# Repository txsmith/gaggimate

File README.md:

This project upgrades a Gaggia espresso machine with smart controls to improve your coffee-making experience. By adding a display and custom electronics, you can monitor and control the machine more easily.

## Features

- **Temperature Control**: Monitor the boiler temperature to ensure optimal brewing conditions.
- **Brew timer**: Set a target duration and run the brewing for the specific time.
- **Steam and Hot Water mode**: Control the pump and valve to run the respective task.
- **Safety Features**: Automatic shutoff if the system becomes unresponsive or overheats.
- **User Interface**: Simple, intuitive display to control and monitor the machine.

## Screenshots

## Hardware

- **Gaggia Espresso Machine**
- **LilyGo T-RGB 2.1" Display**: Runs the user interface and communicates with the system.
- **ESP-WROOM32 DevKit**: Handles the machine’s low-level control.
- **K-Type M4 Thermocouple with MAX6675**: Reads the temperature of the boiler.
- **AC SSR**: Controls the heating element (boiler).
- **2-Channel 5V Relay**: Controls the pump and valve.

## How It Works

The display allows you to control the espresso machine and see live temperature updates. If the machine becomes unresponsive or the temperature goes too high, it will automatically turn off for safety.

## Installation

1. Connect the ESP32-S3 Display, ESP-WROOM32 DevKit, and other components to the Gaggia.
2. Upload the firmware to both microcontrollers.
3. Enjoy your smarter coffee-making experience!

## License

This work is licensed under CC BY-NC-SA 4.0. To view a copy of this license, visit https://creativecommons.org/licenses/by-nc-sa/4.0/

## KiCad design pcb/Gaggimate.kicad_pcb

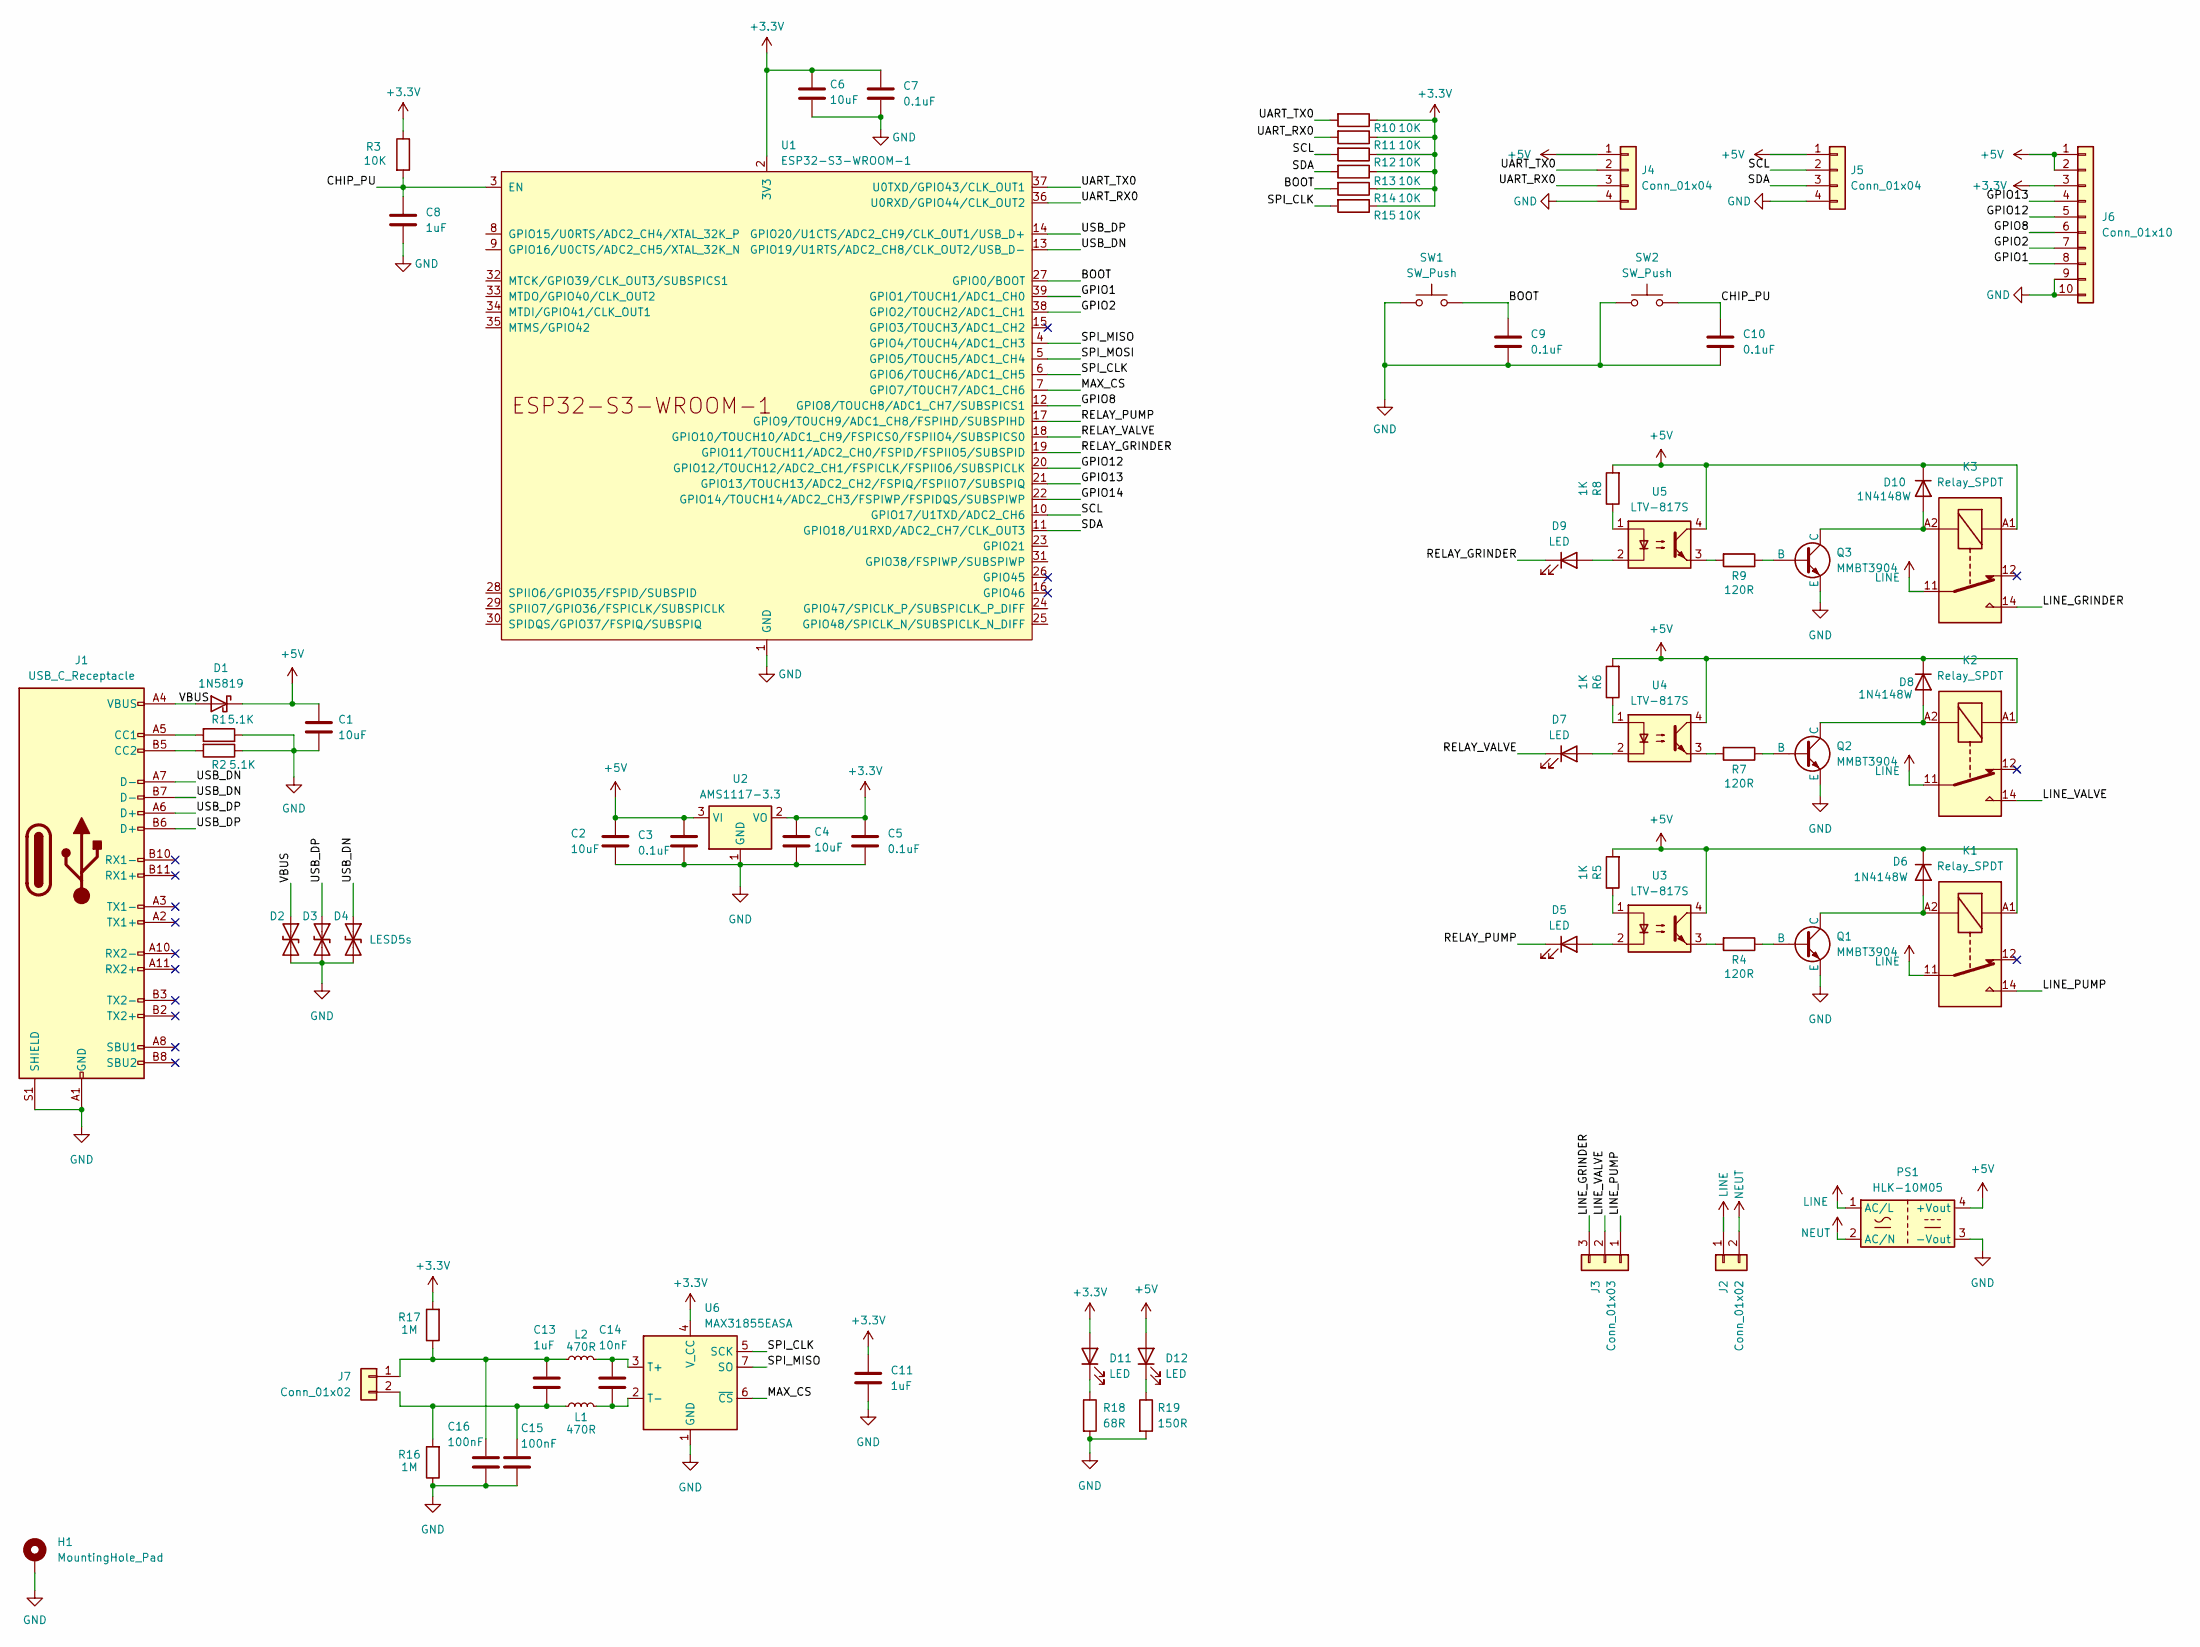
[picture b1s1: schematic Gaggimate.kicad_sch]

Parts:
C1, C2, C4, C6: 10uF; C_0805_2012Metric
C3, C5, C7, C9, C10: 0.1uF; C_0805_2012Metric
C8, C11, C13: 1uF; C_0805_2012Metric
C14: 10nF; C_0805_2012Metric
C15, C16: 100nF; C_0805_2012Metric
D1: 1N5819; D_SOD-123
D2, D3, D4: LESD5s; D_SOD-523
D5, D7, D9, D11, D12: LED; LED_0805_2012Metric
D6, D8, D10: 1N4148W; D_SOD-123
H1: MountingHole_Pad; MountingHole_3.2mm_M3_DIN965_Pad_TopBottom
J1: USB_C_Receptacle; USB_C_Receptacle_HRO_TYPE-C-31-M-12
J2: Conn_01x02; TerminalBlock_bornier-2_P5.08mm
J3: Conn_01x03; TerminalBlock_bornier-3_P5.08mm
J4, J5: Conn_01x04; JST_XH_B4B-XH-A_1x04_P2.50mm_Vertical
J6: Conn_01x10; PinHeader_1x10_P2.54mm_Vertical
J7: Conn_01x02; TerminalBlock_Phoenix_PT-1,5-2-3.5-H_1x02_P3.50mm_Horizontal
K1, K2, K3: Relay_SPDT; Relay_SPDT_Finder_36.11
L1, L2: 470R; L_0805_2012Metric
PS1: HLK-10M05; Converter_ACDC_HiLink_HLK-10Mxx
Q1, Q2, Q3: MMBT3904; SOT-23-3
R1, R2: 5.1K; R_0805_2012Metric
R3, R10, R11, R12, R13, R14, R15: 10K; R_0805_2012Metric
R4, R7, R9: 120R; R_0805_2012Metric
R5, R6, R8: 1K; R_0805_2012Metric
R16, R17: 1M; R_0805_2012Metric
R18: 68R; R_0805_2012Metric
R19: 150R; R_0805_2012Metric
SW1, SW2: SW_Push; SW_SPST_PTS810
U1: ESP32-S3-WROOM-1
U2: AMS1117-3.3; SOT-223-3_TabPin2
U3, U4, U5: LTV-817S; SMDIP-4_W9.53mm
U6: MAX31855EASA; SOIC-8_3.9x4.9mm_P1.27mm

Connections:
+3.3V: C4.1, C5.1, C6.1, C7.1, C11.1, D11.2 (A), J6.3, R3.1, R10.1, R11.1, R12.1, R13.1, R14.1, R15.1, R17.2, U1.2 (3V3), U2.2 (VO), U6.4 (V_CC)
+5V: C1.1, C2.1, C3.1, D1.1 (K), D6.1 (K), D8.1 (K), D10.1 (K), D12.2 (A), J4.1, J5.1, J6.1, J6.2, K1.A1, K2.A1, K3.A1, PS1.4 (+Vout), R5.2, R6.2, R8.2, U2.3 (VI), U3.4, U4.4, U5.4
/BOOT: C9.1, R14.2, SW1.2, U1.27 (GPIO0/BOOT)
/CHIP_PU: C8.1, C10.1, R3.2, SW2.2, U1.3 (EN)
/GPIO1: J6.8, U1.39 (GPIO1/TOUCH1/ADC1_CH0)
/GPIO2: J6.7, U1.38 (GPIO2/TOUCH2/ADC1_CH1)
/GPIO8: J6.6, U1.12 (GPIO8/TOUCH8/ADC1_CH7/SUBSPICS1)
/GPIO12: J6.5, U1.20 (GPIO12/TOUCH12/ADC2_CH1/FSPICLK/FSPIIO6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)
/GPIO13: J6.4, U1.21 (GPIO13/TOUCH13/ADC2_CH2/FSPIQ/FSPIIO7/S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)
/GPIO14: U1.22 (GPIO14/TOUCH14/ADC2_CH3/FSPIWP/FSPIDQS/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)
/LINE_GRINDER: J3.3, K3.14
/LINE_PUMP: J3.1, K1.14
/LINE_VALVE: J3.2, K2.14
/MAX_CS: U1.7 (GPIO7/TOUCH7/ADC1_CH6), U6.6 (~CS)
/RELAY_GRINDER: D9.1 (K), U1.19 (GPIO11/TOUCH11/ADC2_CH0/FSPID/FSPIIO5/S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)
/RELAY_PUMP: D5.1 (K), U1.17 (GPIO9/TOUCH9/ADC1_CH8/FSPIHD/SUBSPIHD)
/RELAY_VALVE: D7.1 (K), U1.18 (GPIO10/TOUCH10/ADC1_CH9/FSPICS0/FSPIIO4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)
/SCL: J5.2, R12.2, U1.10 (GPIO17/U1TXD/ADC2_CH6)
/SDA: J5.3, R13.2, U1.11 (GPIO18/U1RXD/ADC2_CH7/CLK_OUT3)
/SPI_CLK: R15.2, U1.6 (GPIO6/TOUCH6/ADC1_CH5), U6.5 (SCK)
/SPI_MISO: U1.4 (GPIO4/TOUCH4/ADC1_CH3), U6.7 (SO)
/SPI_MOSI: U1.5 (GPIO5/TOUCH5/ADC1_CH4)
/UART_RX0: J4.3, R11.2, U1.36 (U0RXD/GPIO44/CLK_OUT2)
/UART_TX0: J4.2, R10.2, U1.37 (U0TXD/GPIO43/CLK_OUT1)
/USB_DN: D4.1 (A1), J1.A7 (D-), J1.B7 (D-), U1.13 (GPIO19/U1RTS/ADC2_CH8/CLK_OUT2/USB_D-)
/USB_DP: D3.1 (A1), J1.A6 (D+), J1.B6 (D+), U1.14 (GPIO20/U1CTS/ADC2_CH9/CLK_OUT1/USB_D+)
/VBUS: D1.2 (A), D2.1 (A1), J1.A4 (VBUS), J1.A9 (VBUS), J1.B4 (VBUS), J1.B9 (VBUS)
GND: C1.2, C2.2, C3.2, C4.2, C5.2, C6.2, C7.2, C8.2, C9.2, C10.2, C11.2, C15.2, C16.2, D2.2 (A2), D3.2 (A2), D4.2 (A2), H1.1, J1.A1 (GND), J1.A12 (GND), J1.B1 (GND), J1.B12 (GND), J1.S1 (SHIELD), J4.4, J5.4, J6.9, J6.10, PS1.3 (-Vout), Q1.3 (E), Q2.3 (E), Q3.3 (E), R1.1, R2.1, R16.1, R18.2, R19.2, SW1.1, SW2.1, U1.1 (GND), U1.40 (GND), U1.41 (GND), U2.1 (GND), U6.1 (GND); also elsewhere on the board
LINE: J2.1, K1.11, K2.11, K3.11, PS1.1 (AC/L)
NEUT: J2.2, PS1.2 (AC/N)
unnamed: D5.2 (A), U3.2
unnamed: D6.2 (A), K1.A2, Q1.1 (C)
unnamed: D7.2 (A), U4.2
unnamed: D8.2 (A), K2.A2, Q2.1 (C)
unnamed: D9.2 (A), U5.2
unnamed: D10.2 (A), K3.A2, Q3.1 (C)
unnamed: D11.1 (K), R18.1
unnamed: D12.1 (K), R19.1
unnamed: J1.A5 (CC1), R1.2
unnamed: J1.B5 (CC2), R2.2
unnamed: C13.1, C16.1, J7.1, L2.1, R17.1
unnamed: C13.2, C15.1, J7.2, L1.1, R16.2
unnamed: Q1.2 (B), R4.1
unnamed: Q2.2 (B), R7.1
unnamed: Q3.2 (B), R9.1
unnamed: R4.2, U3.3
unnamed: R5.1, U3.1
unnamed: R6.1, U4.1
unnamed: R7.2, U4.3
unnamed: R8.1, U5.1
unnamed: R9.2, U5.3
unnamed: C14.1, L2.2, U6.3 (T+)
unnamed: C14.2, L1.2, U6.2 (T-)

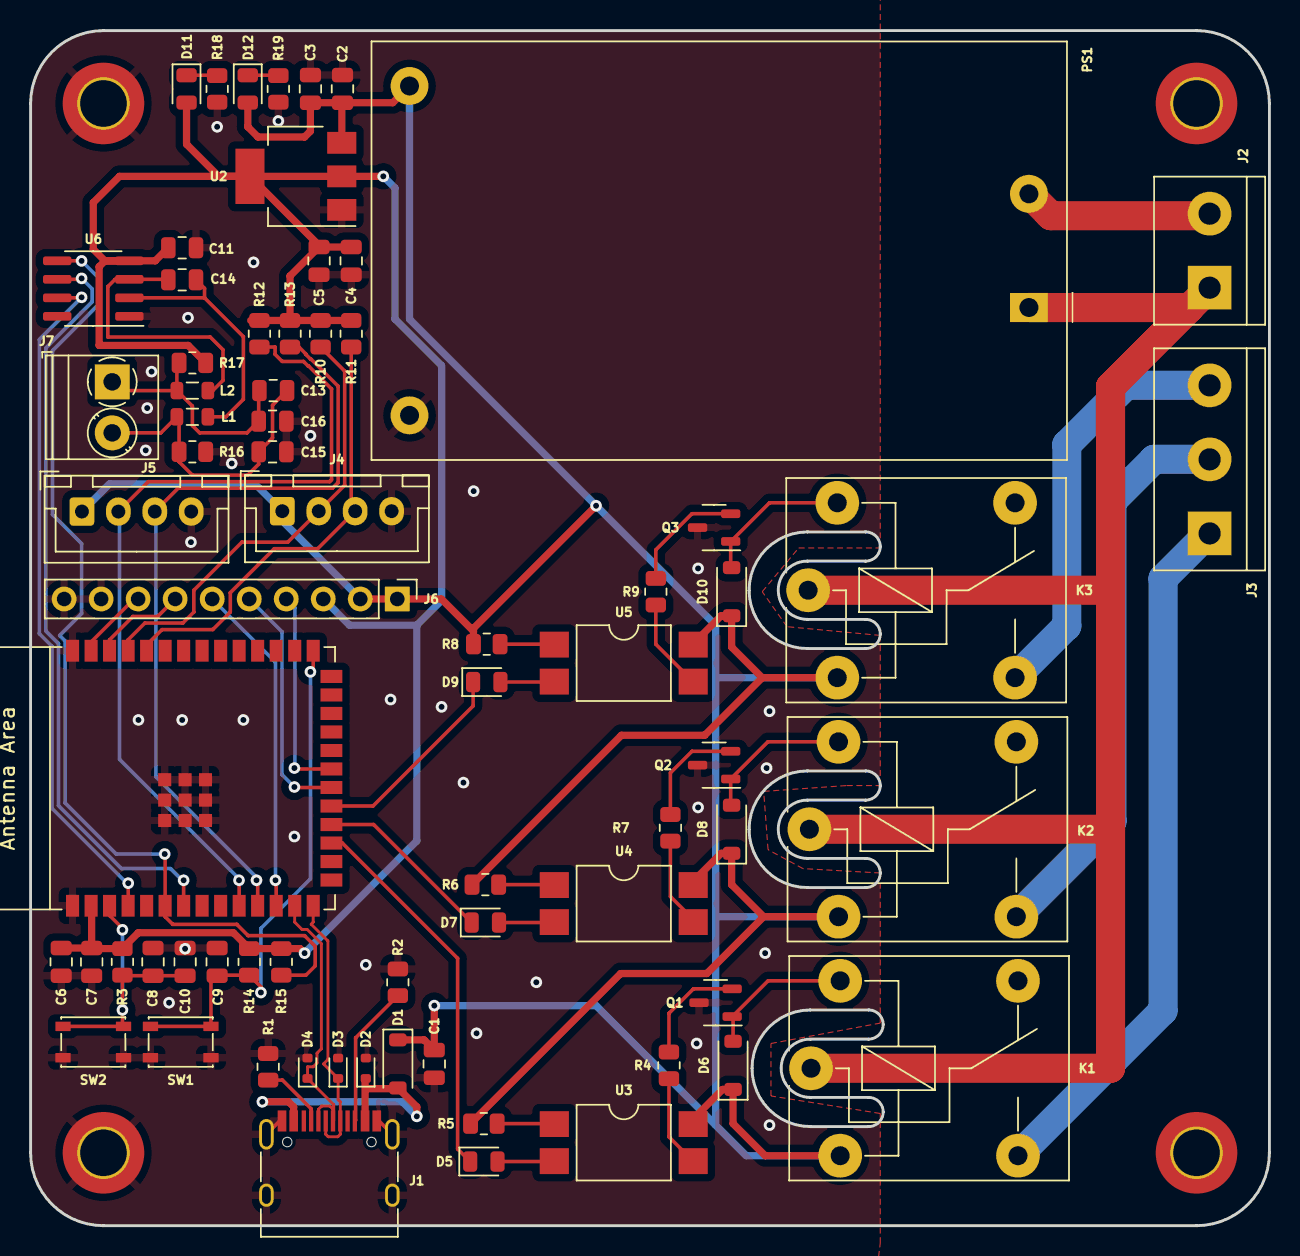
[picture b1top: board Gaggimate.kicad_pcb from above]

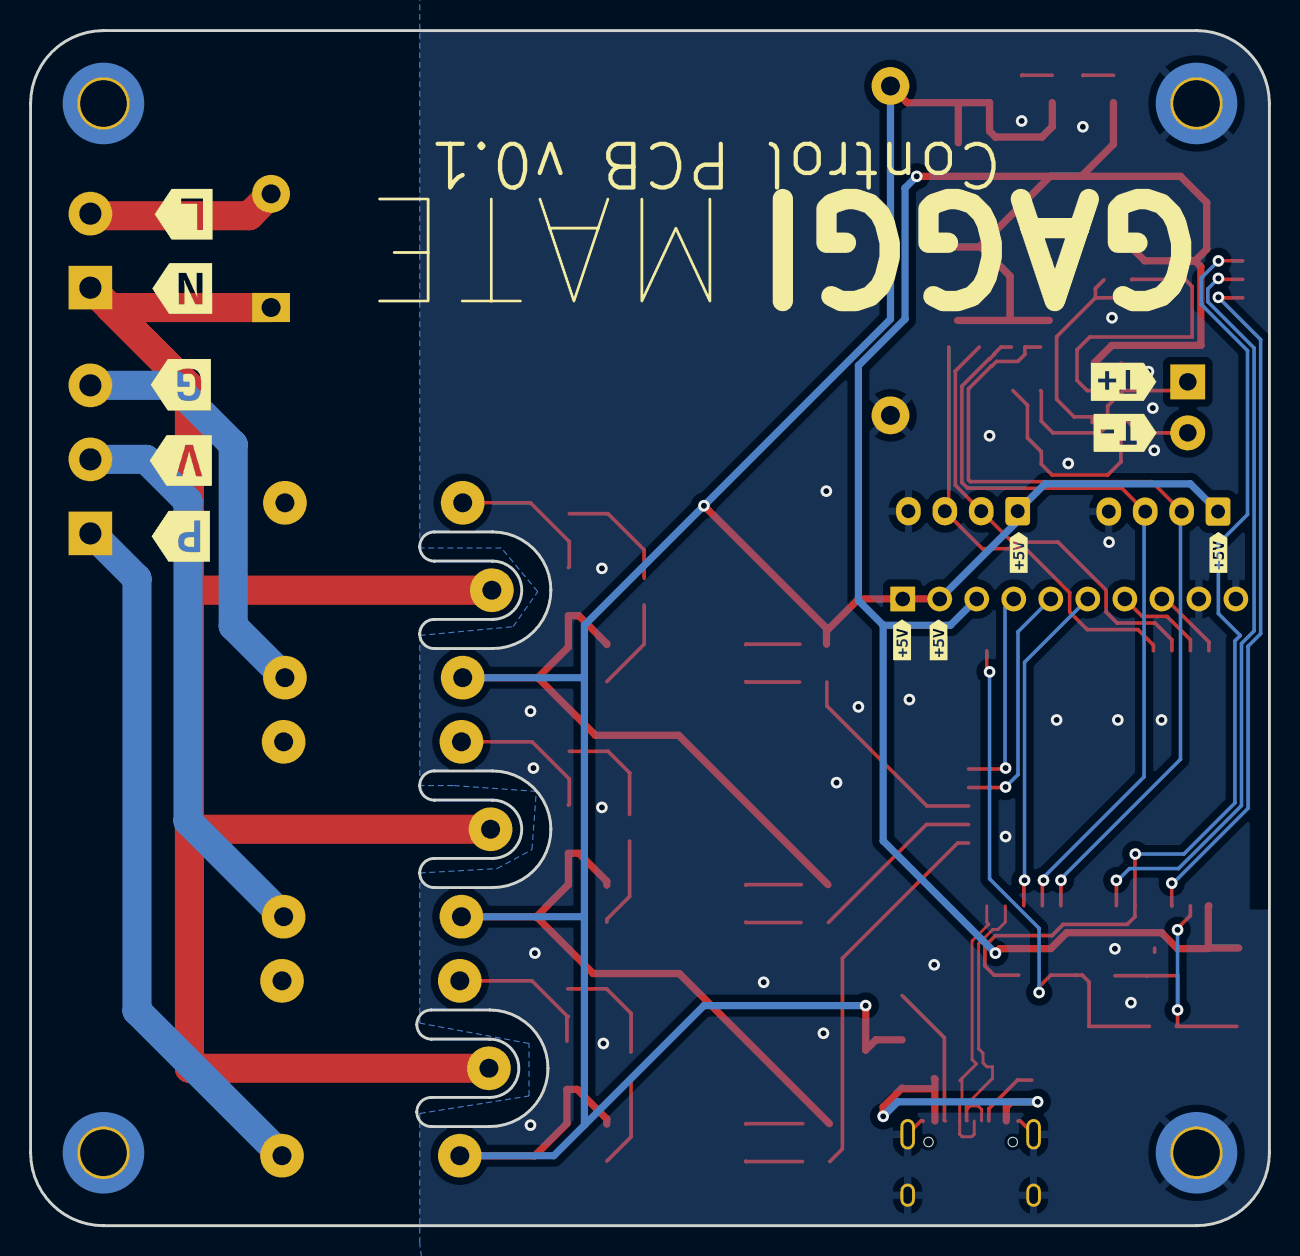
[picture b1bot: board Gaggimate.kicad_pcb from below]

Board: 2 copper layers, 85.0 x 82.0 mm, 85 parts (11 on the bottom side), 51 nets.

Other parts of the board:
H1#2, H1#3, H1#4: MountingHole_Pad; MountingHole_3.2mm_M3_DIN965_Pad_TopBottom
kibuzzard-671E8BF3: G***; kibuzzard-671E8BF3
kibuzzard-671E8C00: G***; kibuzzard-671E8C00
kibuzzard-671E8C4D: G***; kibuzzard-671E8C4D
kibuzzard-671E8C14: G***; kibuzzard-671E8C14
kibuzzard-671E8C44: G***; kibuzzard-671E8C44
kibuzzard-671E8D02, kibuzzard-671E8D02#2, kibuzzard-671E8D02#3, kibuzzard-671E8D02#4: G***; kibuzzard-671E8D02
kibuzzard-671EE717: G***; kibuzzard-671EE717
kibuzzard-671EE722: G***; kibuzzard-671EE722

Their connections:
GND: H1#4.1; also elsewhere on the board

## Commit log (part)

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2024-11-24 fix: Move back connectors to allow expansion to fit
2024-11-24 fix: Fix AC line
2024-11-26 chore: Fix sonarqube issues #2
2024-11-26 chore: Fix sonarqube issues #5
2024-11-27 feat: Rework OTA library, use SPIFFS for web
2024-11-27 doc: Add sonarqube badges
2024-11-27 fix: Fix style css
2024-11-28 fix: Remove auto update for now
2024-12-02 fix: Simplify OTA
2024-12-02 feat: Add wiring diagrams
2024-12-10 feat: Remove docs from readme
2024-12-11 fix: Fix rotation calculation
2024-12-17 fix: Fix partition table for controller
2024-12-19 feat: Finalize first Github OTA functionality
2024-12-19 feat: Add OTA improvements, BLE OTA receiver code
2024-12-19 fix: Fix display build with BLE ota
2024-12-26 Added variant without screwholes
    This screen backplate model fits the GCP better, by having magnets placed lower. This is a version without screw holes.
2025-01-11 feat: Refactor UI code
2025-01-11 fix: Ignore data files
2025-01-12 feat: Add UI changes for volumetric target
2025-01-12 feat: Add BLE scale library
2025-01-14 feat: Rework UI, add waveshare driver, add BLE preparation
2025-01-17 fix: Remove reset
2025-01-18 feat: Allow skipping preinfusion
2025-01-18 fix: Fix formatting
2025-01-20 fix: Clean up brew phase code
2025-01-25 fix: Fix pid bug with temp offset
2025-01-30 feat: Pre-infusion now pumps with the valve open
2025-01-30 feat: Add plugin for automatic boiler refill
2025-01-30 fix: Fix ui files
2025-01-31 feat: Add simple predictive scale feature
2025-02-01 fix: Raise predictive time
2025-02-01 feat: Add MQTT integration with new Web UI
2025-02-01 Aading mqtt user and password
    WIP
2025-02-01 MQTT fix
2025-02-01 fix: Fix sonarqube issue
2025-02-01 fix: Fix header declaration
2025-02-04 fix: Use flex grow for progress bars instead of pixels
2025-02-05 feat: Allow to configure pressurize time
2025-02-05 fix: Fix predictive flow
2025-02-05 fix: Fix filesystem OTA
2025-02-11 fix: Cleanup before board v2
2025-02-15 Added grind mode
2025-03-09 feat: Add felicita arc, fix Eureka scales
2025-03-15 feat: Add button control (#139)
    * added brew button on
    * brew button functionality
    * added steam button actions
    * revert dev changes
    * revert
    * feat: Finish button control code
2025-03-16 feat: Add temperature graph to web ui (#143)
2025-03-16 fix: Fix adding nightly version
    * fix: Add nightly version to build
    * fix: Fix adding version to nightly
2025-03-16 fix: Fix build
2025-03-16 feat: Raise weight output limit to 250 (#149)
    Fixes #138
2025-03-17 fix: Fix captive portal (#152)
    * fix: Fix captive portal
    * fix: Remove unused HTML
2025-03-18 fix: Raise delay between OTA messages
2025-03-19 fix: Add LPF for heater
2025-03-19 feat: Fix v1.4.0 bugs, add better scale and grind control (#158)
2025-04-01 Fixed indent
    Fixed indent
2025-04-01 fix: Fix jumping into brewscreen (#168)
    Fixes #160
2025-04-06 fix: Fix freertos includes
2025-04-06 feat: Make standby timeout configurable (#172)
    Fixes #120
2025-04-10 feat: Add PID Autotune (#176)
    * feat: Add profile edit screen
    * feat: Add PID Autotune
    * fix: Hide future menu options again
    * fix: Remove unused css
2025-05-01 fix: Fix dark mode display of web ui (#182)
2025-05-19 fix: Fix PID heater
2025-05-24 feat: Add pressure gauge, optimize communication (#205)
    * feat: Add pressure display
    * feat: Merge sensor and control data
    * feat: Adjust UI depending on board version
2025-05-29 feat: Improve/fix pump on standard v2, cleanup BLE comms (#210)
2025-06-03 fix: Remove extra options from pid
2025-06-03 fix: Fix nightly workflow
2025-06-06 Add dark background option for profile div (#231)
2025-06-06 fix: Prevent empty favorites
2025-06-06 fix: Fix null division bugs
2025-06-13 fix: Swap out PSM library
2025-06-13 feat: Add styled tooltips
2025-06-14 fix: Add minimum of 1 to duration
2025-06-14 Pressure scaling UI fixes (#235)
    * feat: Introduce profiles (#175)
    * feat: Add profile edit screen
    * fix: Fix merge errors
    * feat: Add new profile screen
    * fix: Fix PID heater
    * feat: Add profile progress
2025-06-15 feat: Set grinder adjustment to 0.5g instead of 1g (#245)
2025-06-16 feat: Add Nayrods pump control, flow estimation and volume estimation (#251)
    * feat: Add Nayrods pump control, flow estimation and volume estimation
    * fix: Fix test warning
    * fix: Fix volume estimation
    * feat: Add pressure and flow graphs to web ui
    * fix: Fix controller usage
2025-06-16 fix: Fix duplicate CSS
2025-06-27 Allowing any float value for the auto adjust brew and grind delay values. (#265)
2025-06-29 feat: Steam Rework and temperature indicator (#277)
    * feat: Redesign UI for new steam mode
    * Make it green (when ready) (#272)
    * feat: Add UI Changes
    * feat: Make steam pump percentage adjustable
    * feat: Change button control for steam mode
    * feat: Major UI speedup, add auto steam
2025-06-30 fix: Update asynctcp, fix websocket reconnect
2025-06-30 fix: Make pressure bar smoother
2025-06-30 fix: Autoconnect scale when startup mode is brew (#280)
2025-07-04 Add NayrodPID as a submodule
2025-07-09 Hydraulic estimation Kalman based, turbulent flow model
2025-07-09 fix: Remove unused wifi manager
2025-07-09 feat: Allow experimental features to stay in releases (#294)
2025-07-09 fix: Fix wrong flow when no brew is running
2025-07-10 fix: Initialize wifi last
2025-07-10 fix: Fix too verbose logging
2025-07-11 fix: Replace wifi manager
2025-07-13 Fix Chart resize on screen rotation (#303)
2025-07-14 Update BLEScalePlugin.cpp for WeighMyBru Scale Support (#284)
    * Update BLEScalePlugin.cpp for WeighMyBru Scale Support
    * Added WeighMyBru Scale Support & Updated platformio.ini
    * Changed platformio.ini file back to original
    ---------
2025-07-14 Add display theme application via WebUI (#282)
    * Add theme application
    * Revert SLS edit
    * Fix newlines
    * Fix settings, change colors
    * No need to trigger dirty
2025-07-14 feat: Add first shot on history (#297)
    * feat: Add first shot on history
    * fix: Fix too verbose logging
    * fix: Fix too verbose error logging
    * feat: Finish first shot of shot history
    * fix: Fix data change
    * fix: Fix estimator
2025-07-17 Move Save Preferences button on OTA page and fix overflow issues (#305)
    * move "Save preferences" button on OTA page, fix overflow issues on OTA and Settings page
    The only real changes are to /web/src/pages/OTA/index.jsx and /web/src/pages/Settings/index.jsx, the rest are from running the prettier command
    Moved the "Save preferences" button to the div containing the Update channel selector to clarify that the button saves the update channel chosen
    Added flex-wrap and gap-y-2 to the div containing the Update-buttons to allow the buttons to stack vertically when there is not enough width to stack them horizontally
    * change flex gap to gap-y-1 on container for Update-buttons to match gap be
2025-07-22 feat: Turn down Autotune shutoff temp (#313)
    * feat: Turn down Autotune shutoff temp
    * fix: Implement code review
2025-07-23 fix: Add back smoothing in pressure controller (#319)
2025-07-26 feat: Allow flow control with pressure limit (#320)
    * feat: Allow flow control with pressure limit
    * fix: Cleanup unused code
    * feat: Allow controlling flow from profile
    * fix: Add codereview feedback
    * fix: Fix unused variable
    * fix: Fix flow control to use pump not puck flow
2025-07-27 fix: Feed back manual control into pressure controller (#324)
2025-07-27 Fix some bugs in T-Display code (#331)
2025-07-28 fix: Fix responsive bugs
2025-07-29 fix: Try smooth down pressure control
2025-08-01 feat: Add headless target for ESP32-S3 XIAO and ESP32-S3 Supermini
2025-08-12 feat: Use flow control for steam on Pro
2025-08-12 fix: Fix reset logic for Waveshare 2.1 screen
2025-08-12 fix: Fix standby icon on light screen
2025-08-13 Daisy UI Migration (#355)
    * Add Daisy Ui (#339)
    * Initial Daisy Ui transition and 4 themes to start
    * Update Ui
    * Fix SonarCloud issues
    * Remove Computed Single line Chart Register
    * Use JSX syntax
2025-08-14 Update BLEScalePlugin.cpp for Aliexpress myscale support (#353)
    * Update BLEScalePlugin.cpp for Aliexpress myscale support
    Added call to myscale Aliexprss cheap scale in conjunction with https://github.com/gaggimate/esp-arduino-ble-scales/pull/11
    * Fixed issue where the bluetooth scale was taring too late (at brew start).
    If the scale had a higher value than the voulumetric setpoint at start,
    the tare would not happen in time and the brew would finish.
    The controller now tares the bluetooth scale before starting the brew and at the same time as it issues controller->tare() to the hardware scale.
2025-08-15 Only render components once (#359)
    * start fixing
    * Fix text wrapping on OTA Page
    * Use DASHBOARD_LAYOUTS
    ---------
2025-08-17 offline font for logo, improve a11y, add .nvmrc file (#367)
    * offline font for logo, improve a11y, add .nvmrc file
    * remove nvm in web folder
    ---------
2025-08-18 fix: Fix adding target
2025-08-20 fix: Fix tcl converter bug
2025-08-21 fix: Switch NTP logic
2025-08-21 fix: Fix compile warnings
2025-08-21 feat: Add experimental outputs for flow estimation
2025-08-21 fix: Revert heating indicator to green/red
2025-08-21 fix: Remove duplicated code
2025-08-21 fix: Cleanup mqtt changes
2025-08-22 fix: Force chart to resize and recalculate dimensions (#378)
2025-08-22 Return ordered favorites based on stored profile order (#381)
    * Update getFavoritedProfiles to return ordered favorites based on stored profile order
    * PR comments fix
    * Fix PR comment
2025-08-22 feat: Some ui fixes, embed font awesome icons
2025-08-23 fix: Skip PWM logic for 0/100 setting of simple pump
2025-08-23 fix: Fix formatting of steam pump percentage field
2025-08-25 feat: Add convert to pro button
2025-08-25 fix: Allow to change adaptive transition
2025-08-25 fix: Fix variation between virtual scales and puck flow
2025-09-01 Fix default created simple brew profile and explicitly set volumetric target operator to GTE. (#401)
2025-09-03 fix: Fix volume estimation in stable
2025-09-04 Remove unused variable (#409)
2025-09-16 Add various guards in BLEScalePlugin (#403)
    * Add some guards to avoid null pointer dereference crashes.
    * More BLE scale guards
    * Even more guards
2025-09-16 Nightly (#419)
    * Enhanced pressure control and raw estimator
    * .h missing
    * Basic flow estimator
    * fix: Fixed coffee weight estimator
    - Cleaned unused variables
    - Fixed estimator for accurate flow estimation (need to tune the first drip criteria)
2025-09-16 fix: Change steam cutoff default
2025-09-17 fix: Fix recompile on every build
2025-09-29 fix: Fix switching volumetric source while running a shot (#439)
    * fix: Fix switching volumetric source while running a shot
    * fix: Allow skip pr-flash
    * fix: Resolve pr feedback
    * fix: Resolve pr feedback
2025-09-29 fix: Rewrite scripts to analyze support file (#440)
2025-10-01 Optimize/shot history + Storage indicator in system & updates (#441)
    * Overview
    The previous CSV history format has been replaced by a compact binary format written directly to SPIFFS to reduce CPU time and flash wear from frequent string allocations / formatting. Each shot is r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
    Incomplete / Interrupted Shots
    If the device reboots or the shot is otherwise interrupted before finalization, `sampleCount` and `durationMs` remain 0 in the header. Recovery logic:
    - Listing (`req:history:list`) infers `samples` and `duration` by: `(fileSize - headerSize) / sampleSize` and reading the last full sample's `t`.
    - Binary downloa
2025-10-02 fix: Fix some responsive bugs
2025-10-05 fix: Fix support info
2025-10-05 fix: Fix grind not shutting off
2025-10-05 Auto-warmup scheduler with per-day scheduling (#387)
    * Remove backwards compatibility checks (old style without days wasn't used except for testing)
    Clean up UI and make it more compact
    * Remove clock icon from time input fields to reduce width of field
    * Change time field to auto width and remove clock icon to minimize space.
    * Revert css change to hide time input clock icon as some platforms require it for input.
    * Increase time field width to better fit the time input icon.
2025-10-08 Overview chart - show profile phases during brew (#450)
    * - Add profile phase markers on overview chart
    - Adjust time axis to show more detail during shot and zoom out as needed
    * - stabilize x-axis
    - ui tweaks
    * Adjust padding
2025-10-18 Make it work with clangd
2025-11-08 Make the visualizer upload dialog use daisyUI styles
2025-11-11 Fix typo in WebUIPlugin
